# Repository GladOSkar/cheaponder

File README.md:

The idea is to put an ESP32 S3 Mini together with a Li-Ion charger and a 3.3V buck-boost regulator into this case:

So i'm going to put a small PCB on the backside of the ESP32 module:

I already tested it and even though it's tight, it should fit.

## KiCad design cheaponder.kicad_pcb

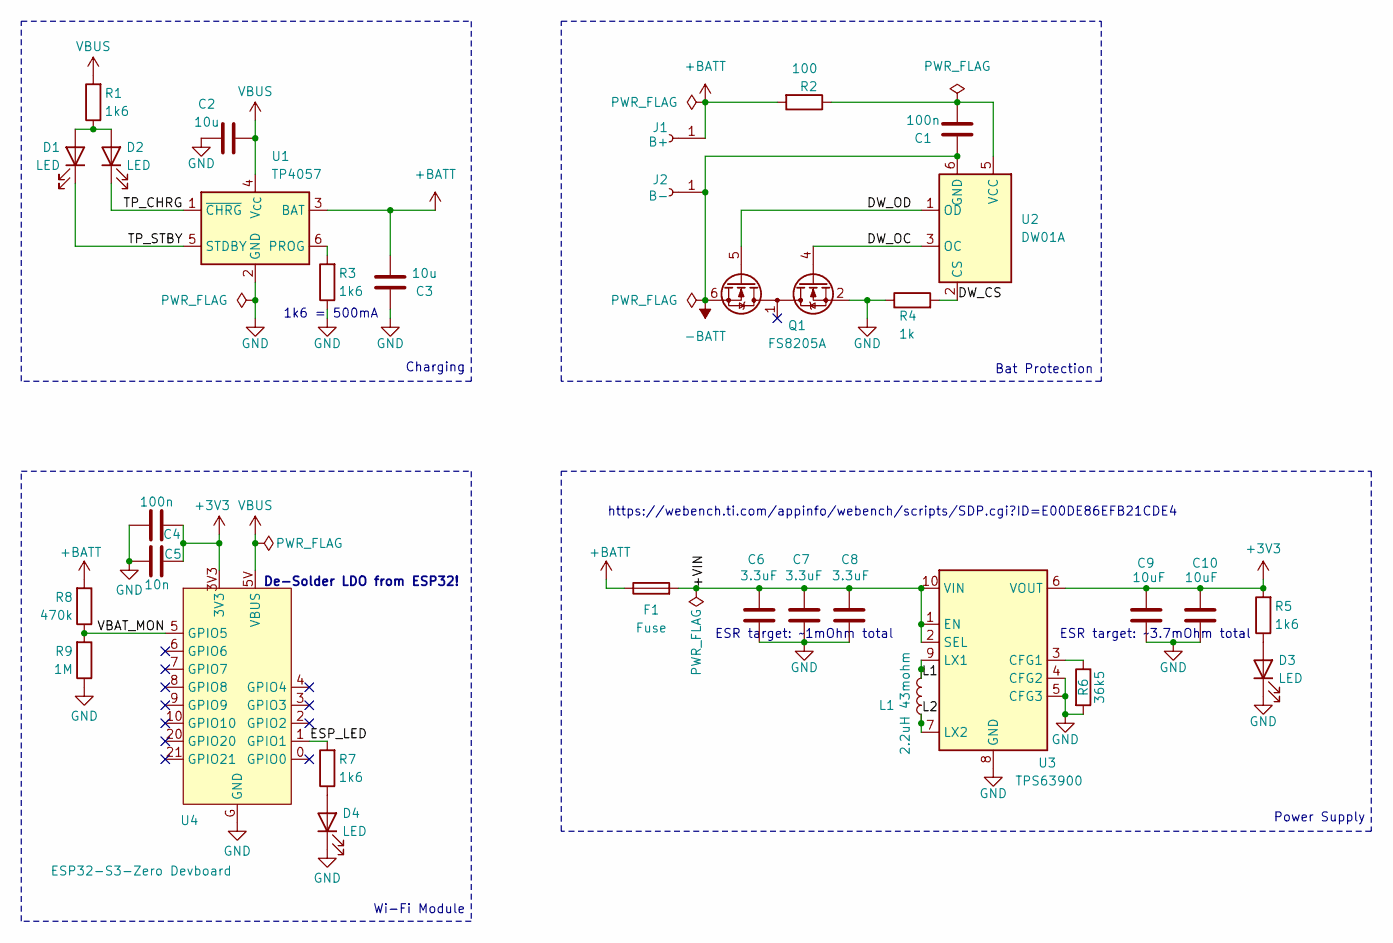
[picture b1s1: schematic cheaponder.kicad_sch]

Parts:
C1, C4: 100n; C_0603_1608Metric
C2: 10u; C_0603_1608Metric
C3: 10u; C_0805_2012Metric
C5: 10n; C_0603_1608Metric
C6, C7, C8: 3.3uF; C_0805_2012Metric
C9, C10: 10uF; C_0805_2012Metric
D1, D2, D3, D4: LED; LED_0603_1608Metric
F1: Fuse; Fuse_0603_1608Metric
J1: B+; pbwire
J2: B-; pbwire
L1: 2.2uH 43mohm; L_Changjiang_FNR5020S
Q1: FS8205A; TSSOP-8_4.4x3mm_P0.65mm
R1, R3, R5, R7: 1k6; R_0603_1608Metric
R2: 100; R_0603_1608Metric
R4: 1k; R_0603_1608Metric
R6: 36k5; R_0603_1608Metric
R8: 470k; R_0603_1608Metric
R9: 1M; R_0603_1608Metric
U1: TP4057; TSOT-23-6
U2: DW01A; SOT-23-6
U3: TPS63900; WSON-10-1EP_2.5x2.5mm_P0.5mm_EP1.2x2mm_ThermalVias
U4: ESP32-S3-Zero Devboard; ESP32_C3_SuperMini

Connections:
+3V3: C4.2, C5.1, C9.2, C10.2, R5.2, U3.6 (VOUT), U4.3V3
+BATT: C3.2, F1.1, J1.1, R2.2, R8.2, U1.3 (BAT)
-BATT: C1.1, J2.1, Q1.6 (S2), Q1.7 (S2), U2.6 (GND)
/+VIN: C6.2, C7.2, C8.2, F1.2, U3.1 (EN), U3.2 (SEL), U3.10 (VIN)
/DW_CS: R4.2, U2.2 (CS)
/DW_OC: Q1.4 (G1), U2.3 (OC)
/DW_OD: Q1.5 (G2), U2.1 (OD)
/ESP_LED: R7.2, U4.1 (GPIO1)
/L1: L1.2, U3.9 (LX1)
/L2: L1.1, U3.7 (LX2)
/TP_CHRG: D2.1 (K), U1.1 (~CHRG)
/TP_STBY: D1.1 (K), U1.5 (STDBY)
/VBAT_MON: R8.1, R9.2, U4.5 (GPIO5)
GND: C2.1, C3.1, C4.1, C5.2, C6.1, C7.1, C8.1, C9.1, C10.1, D3.1 (K), D4.1 (K), Q1.2 (S1), Q1.3 (S1), R3.1, R4.1, R6.2, R9.1, U1.2 (GND), U3.4 (CFG2), U3.5 (CFG3), U3.8 (GND), U3.11 (GND), U4.G (GND)
unnamed: D1.2 (A), D2.2 (A), R1.1
unnamed: D3.2 (A), R5.1
unnamed: D4.2 (A), R7.1
unnamed: R3.2, U1.6 (PROG)
unnamed: C1.2, R2.1, U2.5 (VCC)
unnamed: R6.1, U3.3 (CFG1)
VBUS: C2.2, R1.2, U1.4 (V_{CC}), U4.5V (VBUS)

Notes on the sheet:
De-Solder LDO from ESP32!
Charging
ESR target: ~1mOhm total
1k6 = 500mA
Power Supply
Wi-Fi Module
Bat Protection
ESR target: ~3.7mOhm total
https://webench.ti.com/appinfo/webench/scripts/SDP.cgi?ID=E00DE86EFB21CDE4

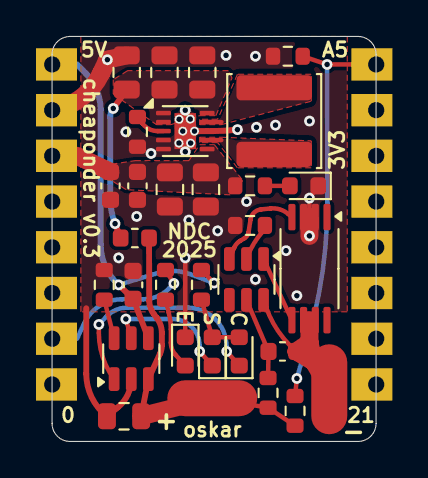
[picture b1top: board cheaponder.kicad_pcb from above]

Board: 2 copper layers, 18.0 x 22.5 mm, 32 parts (1 on the bottom side), 21 nets.

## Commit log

2025-07-21 Update to KiCAD 9
2025-07-21 Fix link and add comment
2025-07-23 Implement some of Max' Feedback
2025-07-23 New 3D model for ESP, photos, Readme
2025-07-24 Relayout to accomodate bigger cap and put LEDs where we can see them
2025-07-25 Add comment and fix trace distance
